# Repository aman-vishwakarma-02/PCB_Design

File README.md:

# PCB Design Projects  
**From Concept to Copper Board — A Small Beginning**

## About
This repository contains PCB design projects developed using **KiCad** as part of my learning and professional journey. The focus is on schematic design, PCB layout, signal integrity considerations, and manufacturable board designs.

## Projects Included

### Arduino UNO Board
### ESP32

### L298N Motor Driver Module

### Four-Layer IoT Development Board
- Multi-layer PCB design  
- Focus on signal integrity and power distribution  
- Designed for IoT and embedded applications  

## Tools & Technologies
- KiCad (Schematic & PCB Layout)  
- Multi-layer PCB design  
- Signal Integrity (SI) basics  
- Power Distribution Network (PDN)  
- DFM / DFA considerations  

## Learning Outcomes
- Understanding the PCB design workflow  
- Component placement and routing techniques  
- Designing manufacturable and reliable boards  
- Exposure to embedded and IoT hardware design

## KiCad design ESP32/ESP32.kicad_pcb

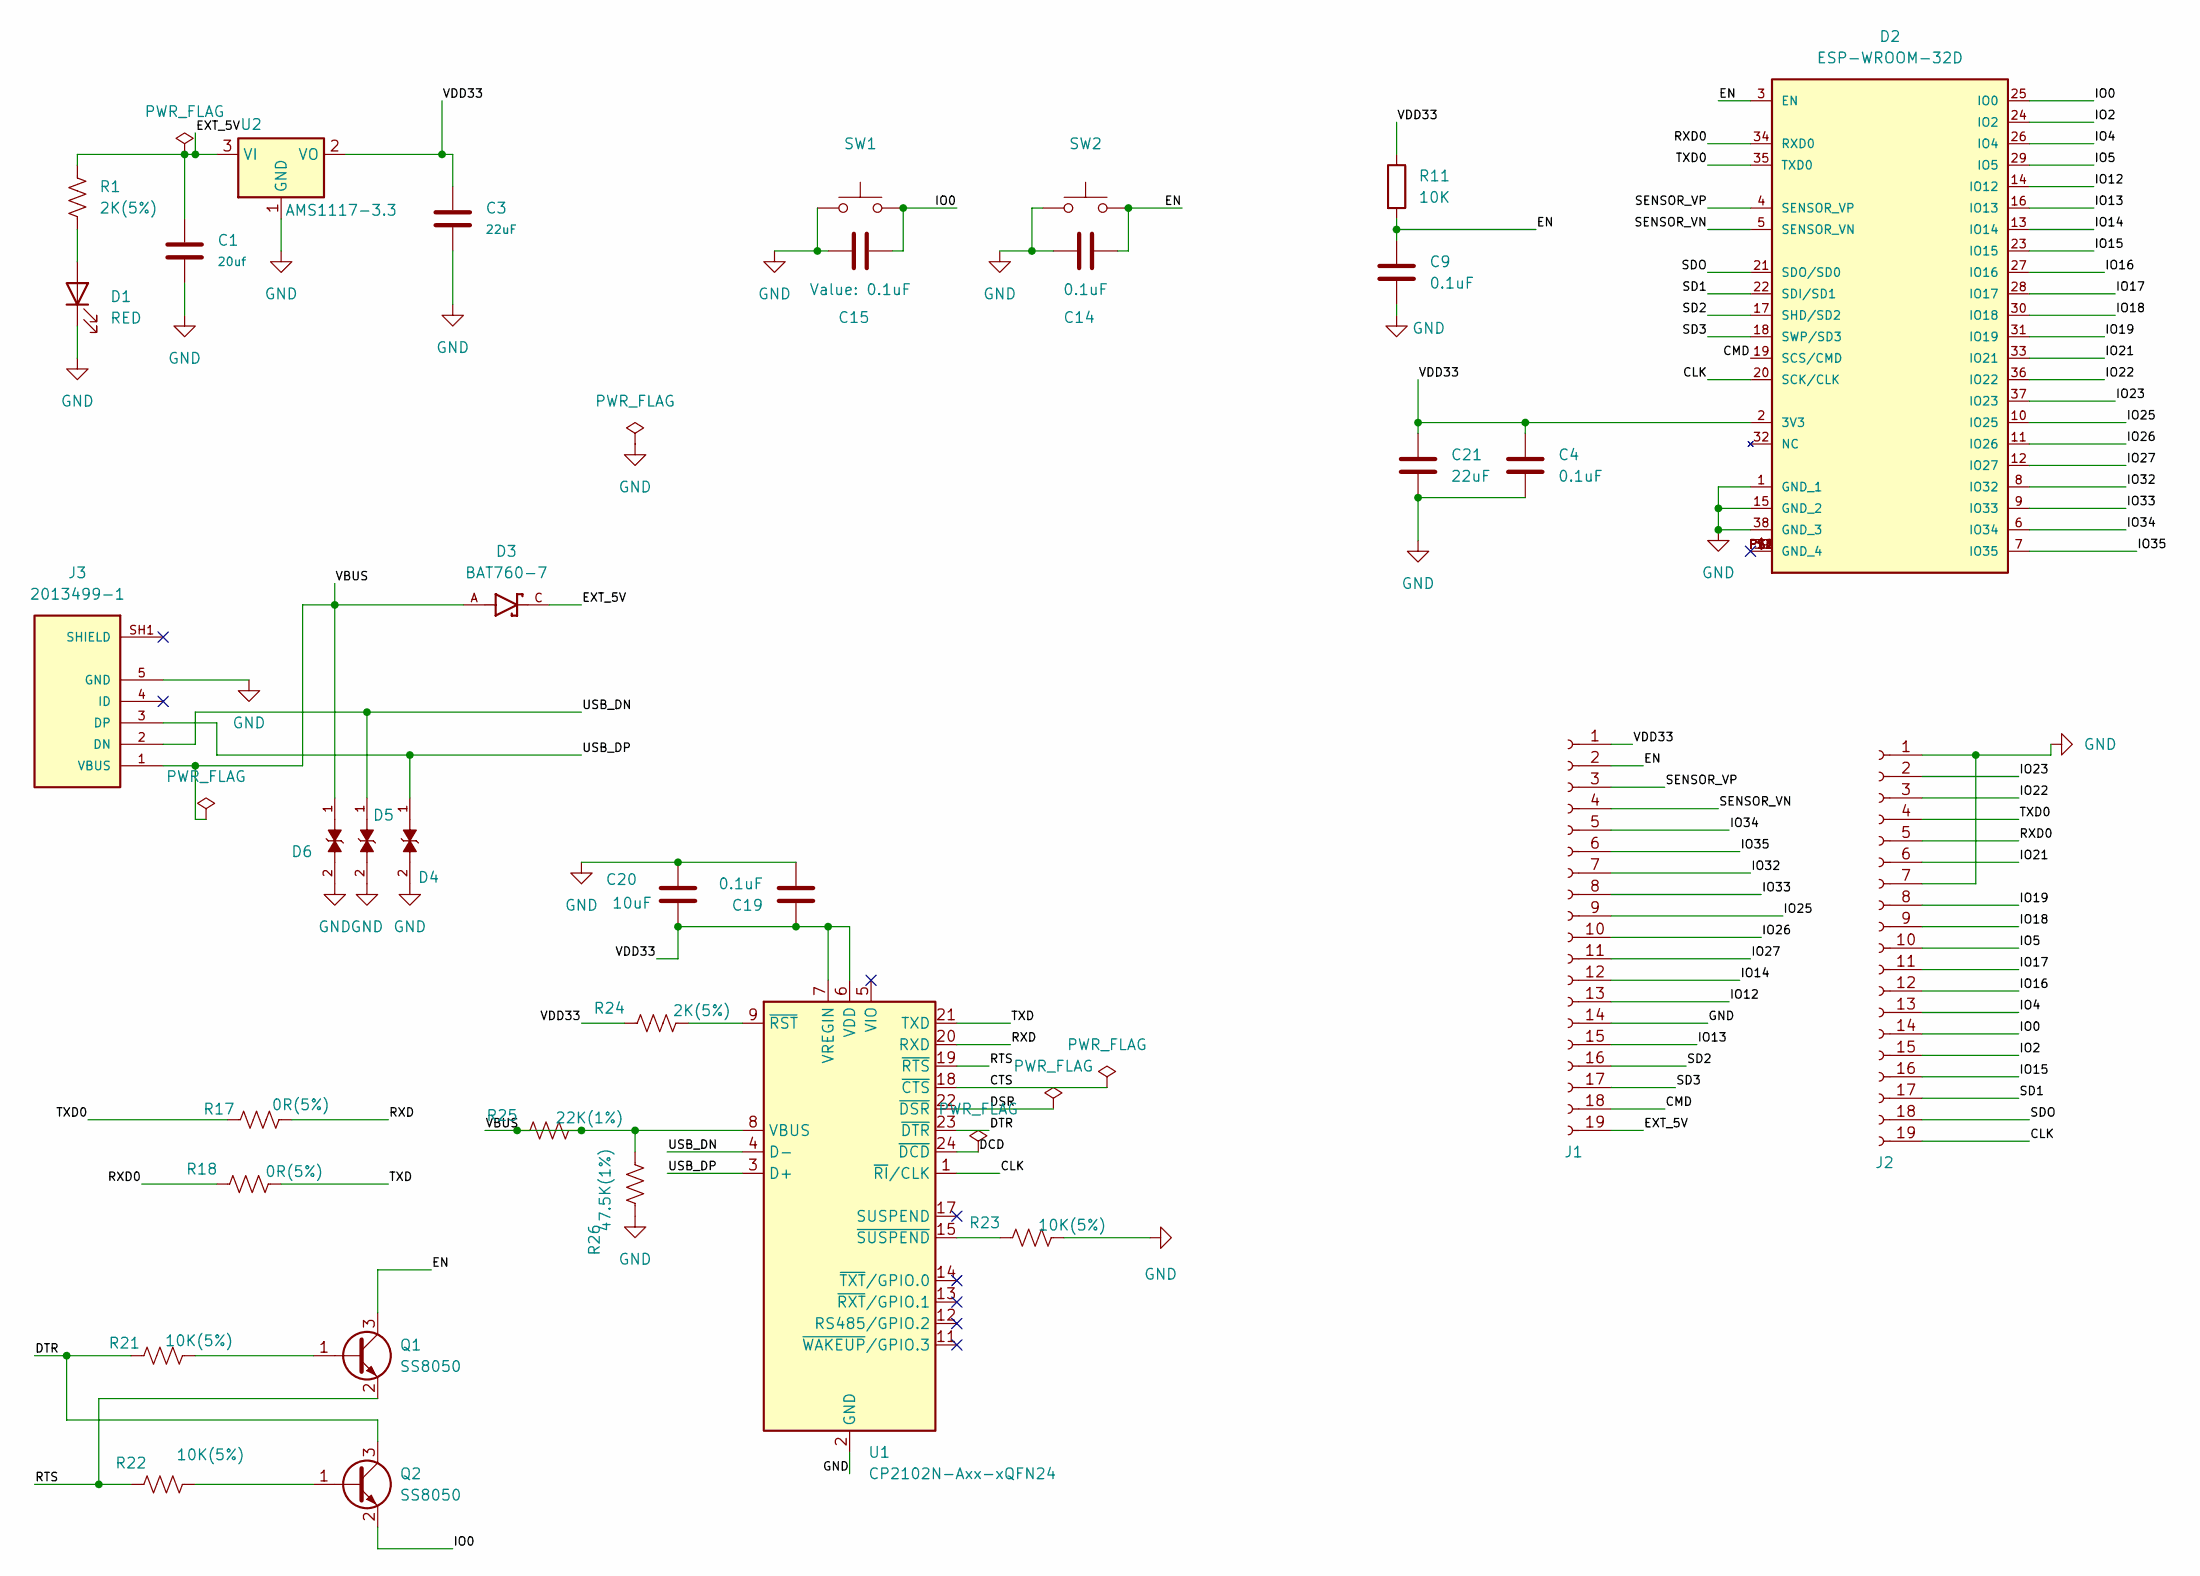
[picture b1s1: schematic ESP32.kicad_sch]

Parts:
C1: 20uf; C_0201_0603Metric
C3, C21: 22uF; C_0201_0603Metric
C4, C9, C14, C15, C19: 0.1uF; C_01005_0402Metric
C20: 10uF; C_0201_0603Metric
D1: RED; D_0201_0603Metric
D2: ESP-WROOM-32D; ESPWROOM32D; MOUSER_PART_NUMBER 356-ESP-WROOM-32D
D3: BAT760-7; SOD2513X120N; PARTREV 9-2
D4, D5, D6: LESD5D5.0CT1G; TVS_LESD5D5.0CT1G; PARTREV O
J1, J2: PinHeader_1x19_P2.54mm_Vertical
J3: 2013499-1; USB_Micro-B_Molex_47346-0001; PARTREV B5
Q1, Q2: SS8050; SOT-23
R1, R24: 2K(5%); R_01005_0402Metric
R11: 10K; R_01005_0402Metric
R17, R18: 0R(5%); R_01005_0402Metric
R21, R22, R23: 10K(5%); R_01005_0402Metric
R25: 22K(1%); R_01005_0402Metric
R26: 47.5K(1%); R_01005_0402Metric
SW1, SW2: SW_Push; SW_Push_SPST_NO_Alps_SKRK
U1: CP2102N-Axx-xQFN24; QFN-24-1EP_4x4mm_P0.5mm_EP2.6x2.6mm
U2: AMS1117-3.3; SOT-223-3_TabPin2

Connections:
/CLK: D2.20 (SCK/CLK), J2.19, U1.1 (~RI/CLK)
/CMD: D2.19 (SCS/CMD), J1.18
/CTS: U1.18 (~CTS)
/DCD: U1.24 (~DCD)
/DSR: U1.22 (~DSR)
/DTR: Q2.3 (C), R21.1, U1.23 (~DTR)
/EN: C9.1, C14.2, D2.3 (EN), J1.2, Q1.3 (C), R11.2, SW2.2
/EXT_5V: C1.1, D3.C, J1.19, R1.1, U2.3 (VI)
/IO0: C15.2, D2.25 (IO0), J2.14, Q2.2 (E), SW1.2
/IO2: D2.24 (IO2), J2.15
/IO4: D2.26 (IO4), J2.13
/IO5: D2.29 (IO5), J2.10
/IO12: D2.14 (IO12), J1.13
/IO13: D2.16 (IO13), J1.15
/IO14: D2.13 (IO14), J1.12
/IO15: D2.23 (IO15), J2.16
/IO16: D2.27 (IO16), J2.12
/IO17: D2.28 (IO17), J2.11
/IO18: D2.30 (IO18), J2.9
/IO19: D2.31 (IO19), J2.8
/IO21: D2.33 (IO21), J2.6
/IO22: D2.36 (IO22), J2.3
/IO23: D2.37 (IO23), J2.2
/IO25: D2.10 (IO25), J1.9
/IO26: D2.11 (IO26), J1.10
/IO27: D2.12 (IO27), J1.11
/IO32: D2.8 (IO32), J1.7
/IO33: D2.9 (IO33), J1.8
/IO34: D2.6 (IO34), J1.5
/IO35: D2.7 (IO35), J1.6
/RTS: Q1.2 (E), R22.1, U1.19 (~RTS)
/RXD: R17.2, U1.20 (RXD)
/RXD0: D2.34 (RXD0), J2.5, R18.1
/SD1: D2.22 (SDI/SD1), J2.17
/SD2: D2.17 (SHD/SD2), J1.16
/SD3: D2.18 (SWP/SD3), J1.17
/SDO: D2.21 (SDO/SD0), J2.18
/SENSOR_VN: D2.5 (SENSOR_VN), J1.4
/SENSOR_VP: D2.4 (SENSOR_VP), J1.3
/TXD: R18.2, U1.21 (TXD)
/TXD0: D2.35 (TXD0), J2.4, R17.1
/USB_DN: D5.1, J3.2 (DN), U1.4 (D-)
/USB_DP: D4.1, J3.3 (DP), U1.3 (D+)
/VBUS: D3.A, D6.1, J3.1 (VBUS), R25.1, R25.2, R26.2, U1.8 (VBUS)
/VDD33: C3.1, C4.1, C19.1, C20.1, C21.1, D2.2 (3V3), J1.1, R11.1, R24.1, U1.6 (VDD), U1.7 (VREGIN), U2.2 (VO); also elsewhere on the board
GND: C1.2, C3.2, C4.2, C9.2, C14.1, C15.1, C19.2, C20.2, C21.2, D1.1 (K), D2.1 (GND_1), D2.15 (GND_2), D2.38 (GND_3), D4.2, D5.2, D6.2, J1.14, J2.1, J2.7, J3.5 (GND), R23.2, R26.1, SW1.1, SW2.1, U1.2 (GND), U1.25 (GND), U2.1 (GND); also elsewhere on the board
unnamed: D1.2 (A), R1.2
unnamed: Q1.1 (B), R21.2
unnamed: Q2.1 (B), R22.2
unnamed: R24.2, U1.9 (~RST)
unnamed: R23.1, U1.15 (~SUSPEND)

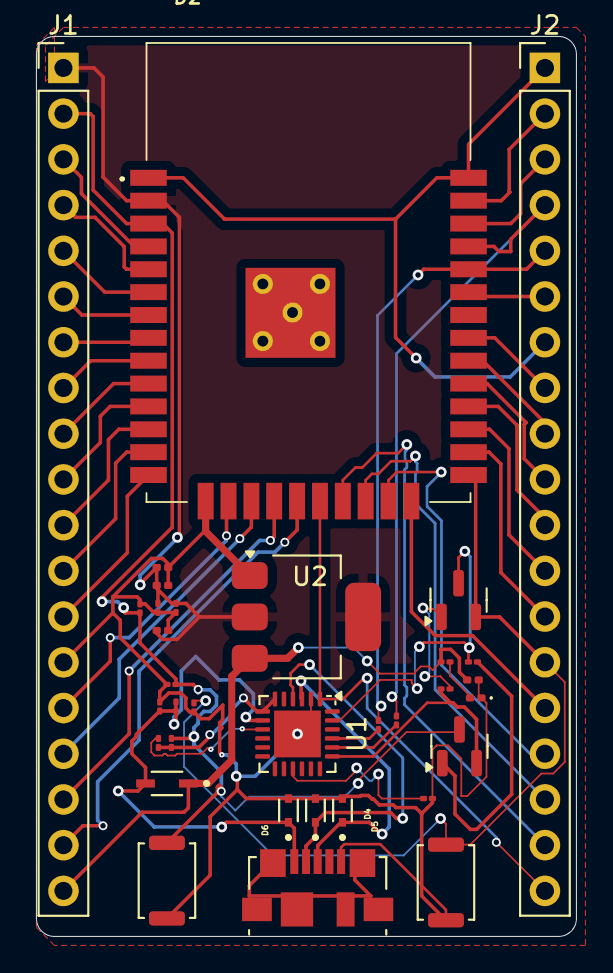
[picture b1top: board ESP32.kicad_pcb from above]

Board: 2 copper layers, 30.0 x 50.0 mm, 34 parts (0 on the bottom side), 48 nets.

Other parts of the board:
C: 22uF; C_0201_0603Metric

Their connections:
/VDD33: C.1; also elsewhere on the board
GND: C.2; also elsewhere on the board

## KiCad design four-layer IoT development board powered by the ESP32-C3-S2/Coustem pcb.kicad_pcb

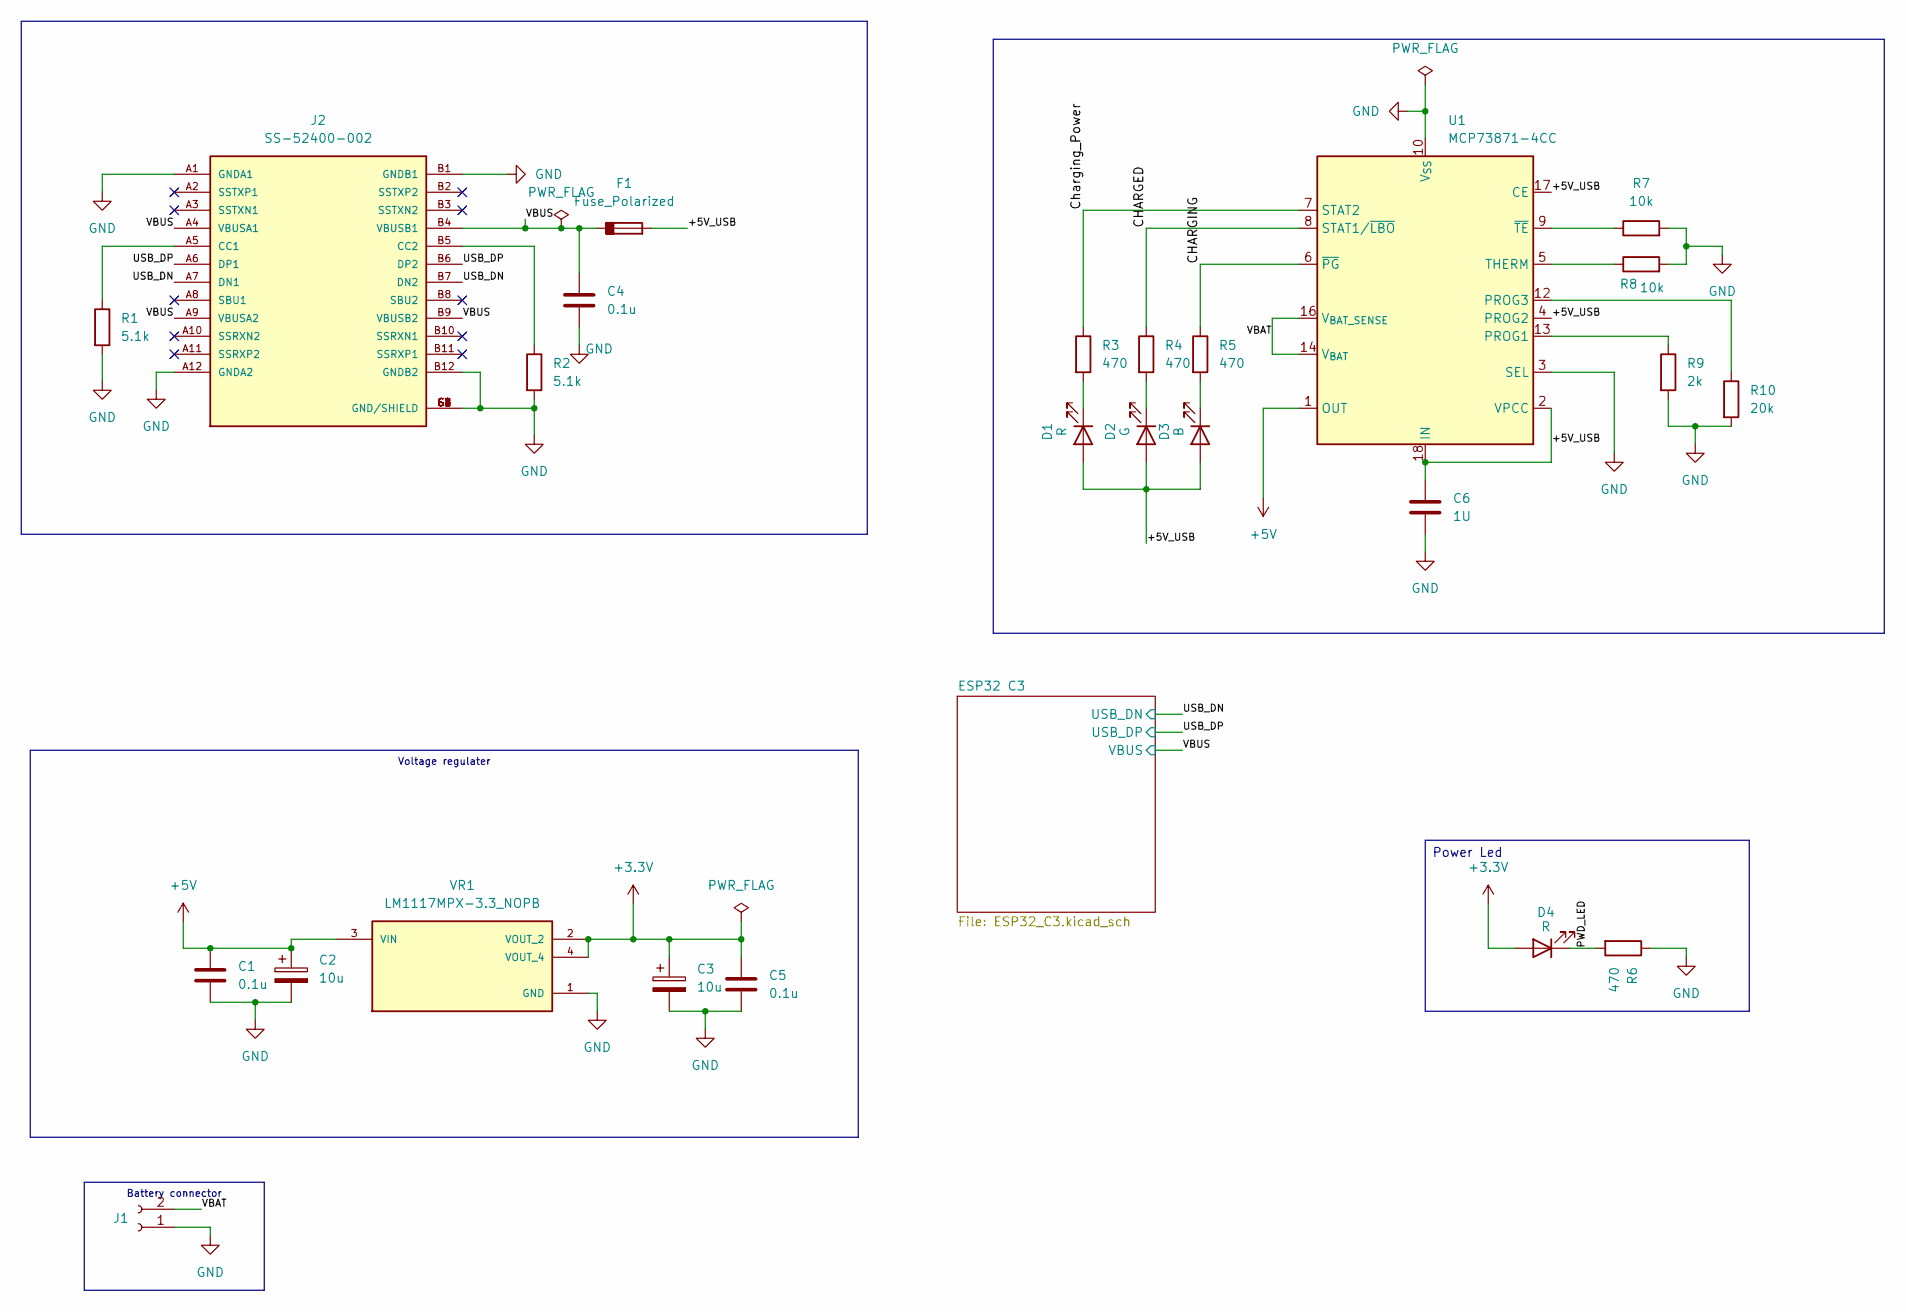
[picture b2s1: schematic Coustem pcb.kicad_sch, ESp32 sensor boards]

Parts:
C1, C4, C5: 0.1u; C_0805_2012Metric
C2, C3: 10u; CP_EIA-2012-15_AVX-P_HandSolder
C6: 1U; C_0805_2012Metric
D1, D4: R; LED_0805_2012Metric
D2: G; LED_0805_2012Metric
D3: B; LED_0805_2012Metric
F1: Fuse_Polarized; Fuse_1206_3216Metric
J1: Conn_01x02_Socket; JST_EH_B2B-EH-A_1x02_P2.50mm_Vertical
J2: SS-52400-002; BELFUSE_SS-52400-002; PARTREV A0
R1, R2: 5.1k; R_0805_2012Metric_Pad1.20x1.40mm_HandSolder
R3, R4, R5, R6: 470; R_0805_2012Metric_Pad1.20x1.40mm_HandSolder
R7, R8: 10k; R_0805_2012Metric_Pad1.20x1.40mm_HandSolder
R9: 2k; R_0805_2012Metric_Pad1.20x1.40mm_HandSolder
R10: 20k; R_0805_2012Metric_Pad1.20x1.40mm_HandSolder
U1: MCP73871-4CC; QFN-20-1EP_4x4mm_P0.5mm_EP2.5x2.5mm
VR1: LM1117MPX-3.3_NOPB; VREG_LM1117MPX-3.3_NOPB; PARTREV O

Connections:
+3.3V: C3.1, C5.1, D4.2 (A), VR1.2 (VOUT_2), VR1.4 (VOUT_4); also elsewhere on the board
+5V: C1.1, C2.1, U1.1 (OUT), U1.20 (OUT), VR1.3 (VIN)
/+5V_USB: C6.1, D1.2 (A), D2.2 (A), D3.2 (A), F1.2, U1.2 (VPCC), U1.4 (PROG2), U1.17 (CE), U1.18 (IN), U1.19 (IN)
/CHARGED: R4.1, U1.8 (STAT1/~LBO)
/CHARGING: R5.1, U1.6 (~PG)
/Charging_Power: R3.1, U1.7 (STAT2)
/PWD_LED: D4.1 (K), R6.2
/USB_DN: J2.A7 (DN1), J2.B7 (DN2); also elsewhere on the board
/USB_DP: J2.A6 (DP1), J2.B6 (DP2); also elsewhere on the board
/VBAT: J1.2, U1.14 (V_{BAT}), U1.15 (V_{BAT}), U1.16 (V_{BAT_SENSE})
/VBUS: C4.1, F1.1, J2.A4 (VBUSA1), J2.A9 (VBUSA2), J2.B4 (VBUSB1), J2.B9 (VBUSB2); also elsewhere on the board
GND: C1.2, C2.2, C3.2, C4.2, C5.2, C6.2, J1.1, J2.A1 (GNDA1), J2.A12 (GNDA2), J2.B1 (GNDB1), J2.B12 (GNDB2), J2.G1 (GND/SHIELD), J2.G2 (GND/SHIELD), J2.G3 (GND/SHIELD), J2.G4 (GND/SHIELD), J2.S1 (GND/SHIELD), J2.S2 (GND/SHIELD), J2.S3 (GND/SHIELD), J2.S4 (GND/SHIELD), R1.2, R2.2, R6.1, R7.2, R8.2, R9.2, R10.2, U1.3 (SEL), U1.10 (V_{SS}), U1.11 (V_{SS}), U1.21 (V_{SS}), VR1.1 (GND); also elsewhere on the board
unnamed: D1.1 (K), R3.2
unnamed: D2.1 (K), R4.2
unnamed: D3.1 (K), R5.2
unnamed: J2.A5 (CC1), R1.1
unnamed: J2.B5 (CC2), R2.1
unnamed: R9.1, U1.13 (PROG1)
unnamed: R10.1, U1.12 (PROG3)
unnamed: R8.1, U1.5 (THERM)
unnamed: R7.1, U1.9 (~TE)

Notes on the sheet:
Power Led
Voltage regulater
Battery connector

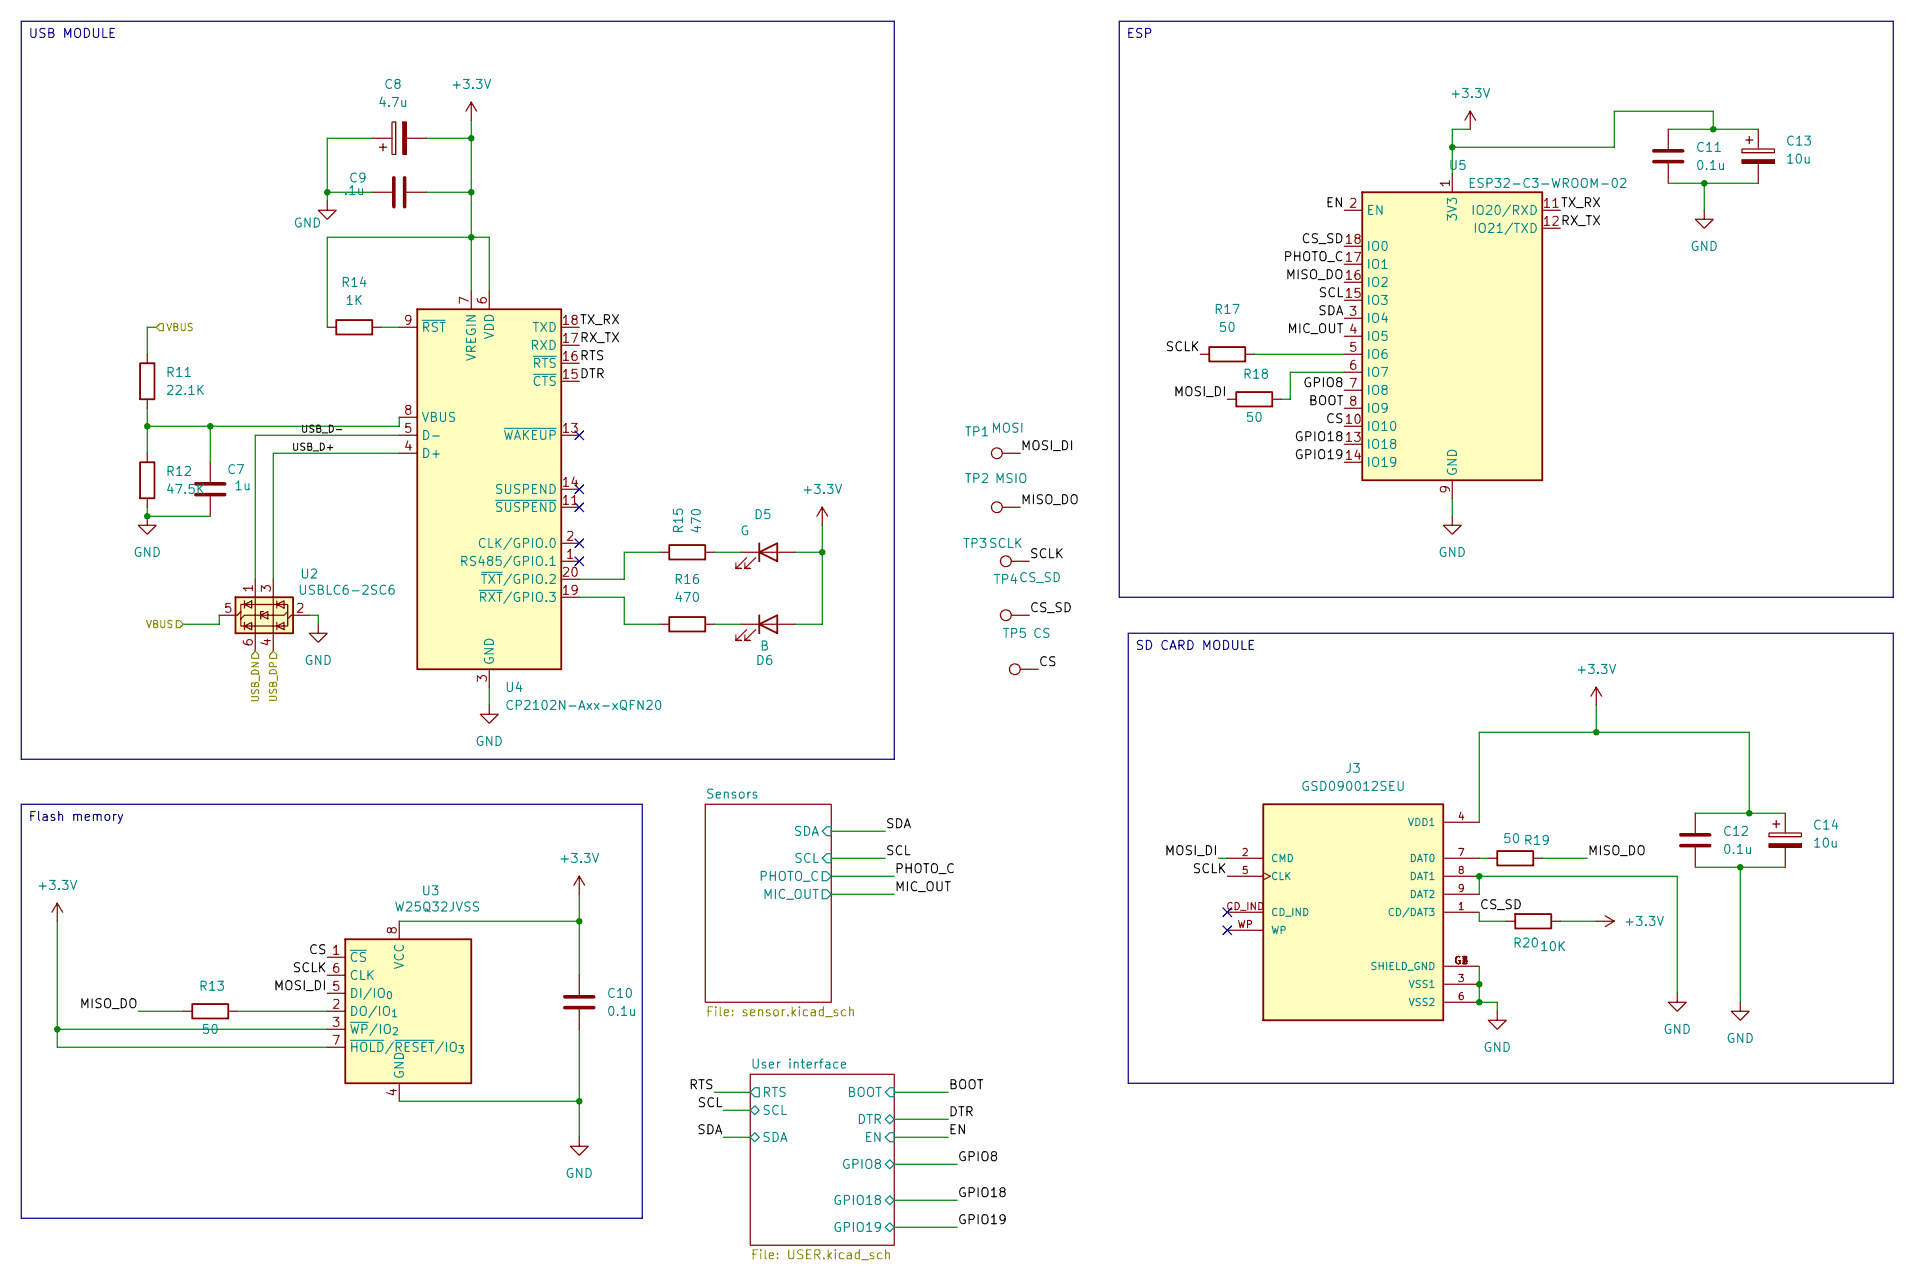
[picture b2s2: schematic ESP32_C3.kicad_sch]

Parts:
C7: 1u; C_0805_2012Metric
C8: 4.7u; CP_EIA-2012-12_Kemet-R_HandSolder
C9: .1u; C_0805_2012Metric
C10, C11, C12: 0.1u; C_0805_2012Metric
C13: 10u; CP_EIA-2012-12_Kemet-R_HandSolder
C14: 10u; C_0805_2012Metric
D5: G; LED_0805_2012Metric
D6: B; LED_0805_2012Metric
J3: GSD090012SEU; AMPHENOL_GSD090012SEU; PARTREV E
R11: 22.1K; R_0805_2012Metric_Pad1.20x1.40mm_HandSolder
R12: 47.5K; R_0805_2012Metric_Pad1.20x1.40mm_HandSolder
R13, R17, R18, R19: 50; R_0805_2012Metric_Pad1.20x1.40mm_HandSolder
R14: 1K; R_0805_2012Metric_Pad1.20x1.40mm_HandSolder
R15, R16: 470; R_0805_2012Metric_Pad1.20x1.40mm_HandSolder
R20: 10K; R_0805_2012Metric_Pad1.20x1.40mm_HandSolder
TP1: MOSI; TestPoint_Pad_D1.0mm
TP2: MSIO; TestPoint_Pad_D1.0mm
TP3: SCLK; TestPoint_Pad_D1.0mm
TP4: CS_SD; TestPoint_Pad_D1.0mm
TP5: CS; TestPoint_Pad_D1.0mm
U2: USBLC6-2SC6; SOT-23-6
U3: W25Q32JVSS; SOIC-8_5.3x5.3mm_P1.27mm
U4: CP2102N-Axx-xQFN20; SiliconLabs_QFN-20-1EP_3x3mm_P0.5mm_EP1.8x1.8mm
U5: ESP32-C3-WROOM-02

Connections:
+3.3V: C8.2, C9.2, C10.1, C11.1, C12.1, C13.1, C14.1, D5.2 (A), D6.2 (A), J3.4 (VDD1), R14.1, R20.1, U3.3 (~WP/IO_{2}), U3.7 (~HOLD/~RESET/IO_{3}), U3.8 (VCC), U4.6 (VDD), U4.7 (VREGIN), U5.1 (3V3); also elsewhere on the board
/ESP32 C3/BOOT: U5.8 (IO9); also elsewhere on the board
/ESP32 C3/CS: TP5.1, U3.1 (~CS), U5.10 (IO10)
/ESP32 C3/CS_SD: J3.1 (CD/DAT3), R20.2, TP4.1, U5.18 (IO0)
/ESP32 C3/DTR: U4.15 (~CTS); also elsewhere on the board
/ESP32 C3/EN: U5.2 (EN); also elsewhere on the board
/ESP32 C3/GPIO8: U5.7 (IO8); also elsewhere on the board
/ESP32 C3/GPIO18: U5.13 (IO18); also elsewhere on the board
/ESP32 C3/GPIO19: U5.14 (IO19); also elsewhere on the board
/ESP32 C3/MIC_OUT: U5.4 (IO5); also elsewhere on the board
/ESP32 C3/MISO_DO: R13.1, R19.2, TP2.1, U5.16 (IO2)
/ESP32 C3/MOSI_DI: J3.2 (CMD), R18.1, TP1.1, U3.5 (DI/IO_{0})
/ESP32 C3/PHOTO_C: U5.17 (IO1); also elsewhere on the board
/ESP32 C3/RTS: U4.16 (~RTS); also elsewhere on the board
/ESP32 C3/RX_TX: U4.17 (RXD), U5.12 (IO21/TXD)
/ESP32 C3/SCL: U5.15 (IO3); also elsewhere on the board
/ESP32 C3/SCLK: J3.5 (CLK), R17.1, TP3.1, U3.6 (CLK)
/ESP32 C3/SDA: U5.3 (IO4); also elsewhere on the board
/ESP32 C3/TX_RX: U4.18 (TXD), U5.11 (IO20/RXD)
/ESP32 C3/USB_D+: U2.3 (I/O2), U4.4 (D+)
/ESP32 C3/USB_D-: U2.1 (I/O1), U4.5 (D-)
/USB_DN: U2.6 (I/O1); also elsewhere on the board
/USB_DP: U2.4 (I/O2); also elsewhere on the board
/VBUS: R11.1, U2.5 (VBUS); also elsewhere on the board
GND: C7.2, C8.1, C9.1, C10.2, C11.2, C12.2, C13.2, C14.2, J3.3 (VSS1), J3.6 (VSS2), J3.8 (DAT1), J3.9 (DAT2), J3.G1 (SHIELD_GND), J3.G2 (SHIELD_GND), J3.G3 (SHIELD_GND), J3.G4 (SHIELD_GND), R12.2, U2.2 (GND), U3.4 (GND), U4.3 (GND), U4.12 (GND), U4.21 (GND), U5.9 (GND), U5.19 (GND); also elsewhere on the board
unnamed: D5.1 (K), R15.2
unnamed: D6.1 (K), R16.2
unnamed: J3.7 (DAT0), R19.1
unnamed: R13.2, U3.2 (DO/IO_{1})
unnamed: C7.1, R11.2, R12.1, U4.8 (VBUS)
unnamed: R14.2, U4.9 (~RST)
unnamed: R16.1, U4.19 (~RXT/GPIO.3)
unnamed: R15.1, U4.20 (~TXT/GPIO.2)
unnamed: R17.2, U5.5 (IO6)
unnamed: R18.2, U5.6 (IO7)

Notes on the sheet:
SD CARD MODULE
ESP
Flash memory
USB MODULE

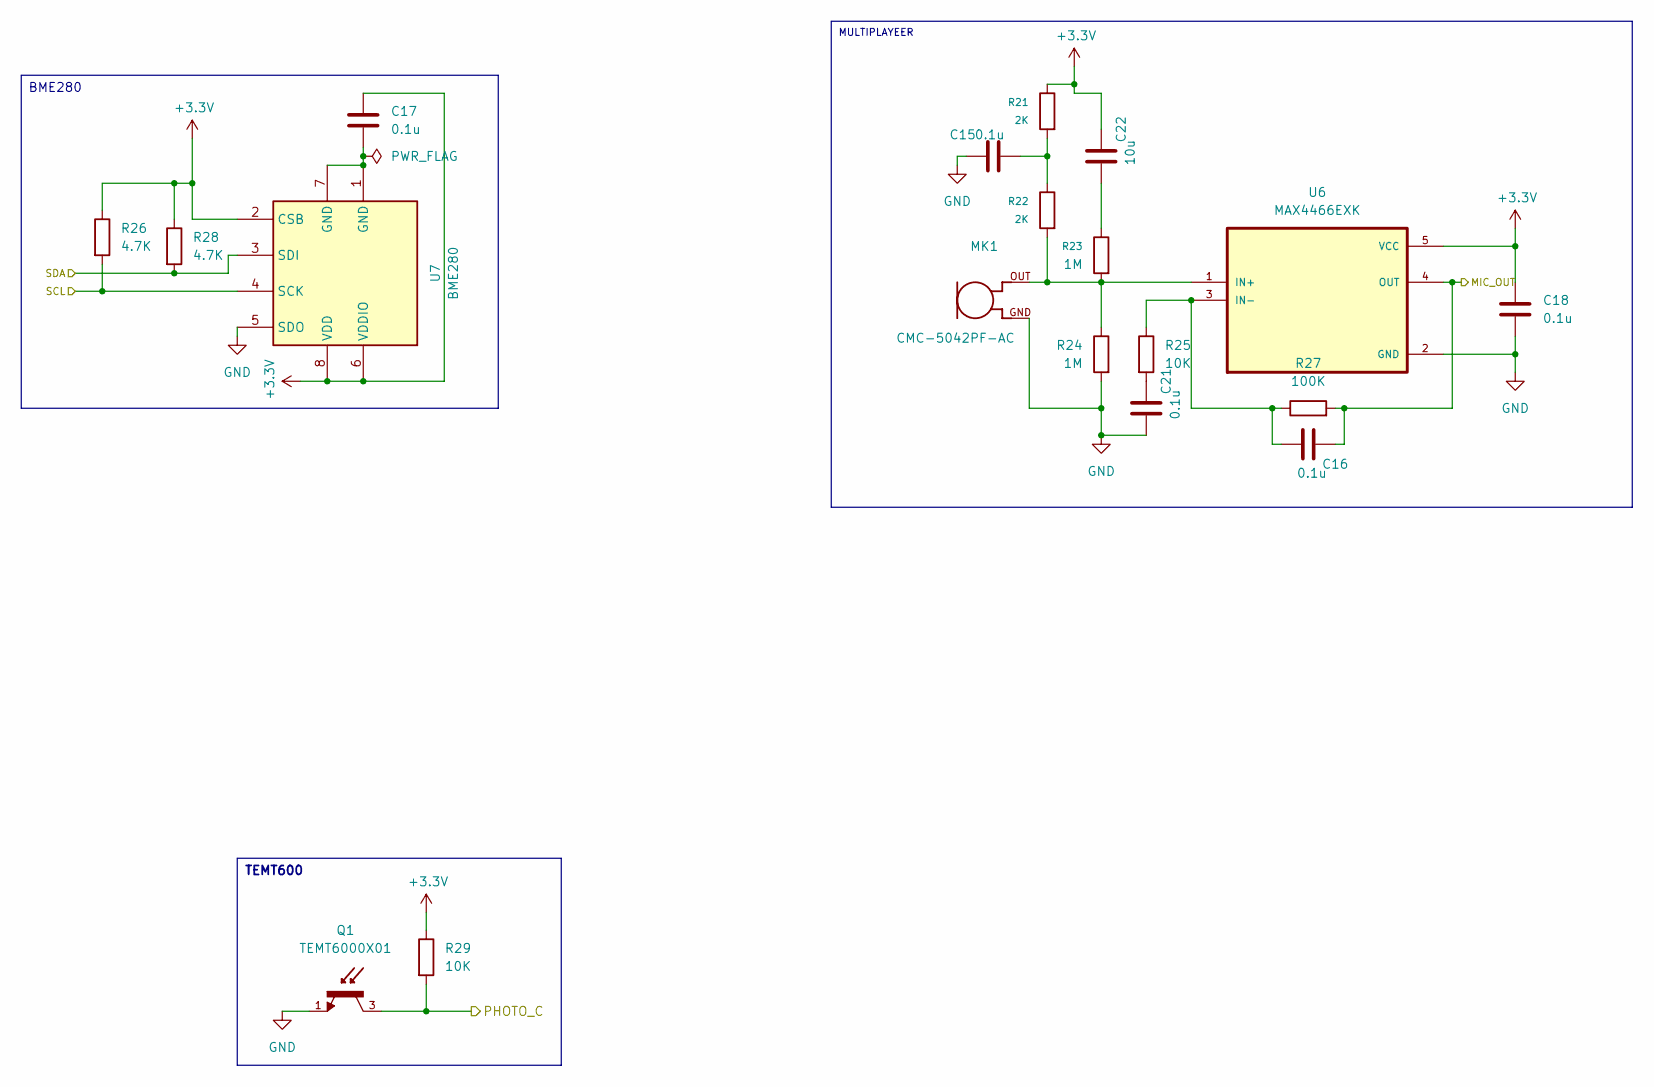
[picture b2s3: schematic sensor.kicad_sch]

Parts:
C15, C16, C17, C18, C21: 0.1u; C_0805_2012Metric
C22: 10u; C_0805_2012Metric
MK1: CMC-5042PF-AC; CUI_CMC-5042PF-AC
Q1: TEMT6000X01; TRANS_TEMT6000X01; PARTREV 1.9; DigiKey_Part_Number 751-1055-1-ND
R21, R22: 2K; R_0805_2012Metric_Pad1.20x1.40mm_HandSolder
R23, R24: 1M; R_0805_2012Metric_Pad1.20x1.40mm_HandSolder
R25, R29: 10K; R_0805_2012Metric_Pad1.20x1.40mm_HandSolder
R26, R28: 4.7K; R_0805_2012Metric_Pad1.20x1.40mm_HandSolder
R27: 100K; R_0805_2012Metric_Pad1.20x1.40mm_HandSolder
U6: MAX4466EXK; SOT65P210X110-5N
U7: BME280; Bosch_LGA-8_2.5x2.5mm_P0.65mm_ClockwisePinNumbering

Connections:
+3.3V: C17.2, C18.2, C22.1, R21.1, R26.1, R28.1, R29.1, U6.5 (VCC), U7.2 (CSB), U7.6 (VDDIO), U7.8 (VDD); also elsewhere on the board
/ESP32 C3/MIC_OUT: C16.1, R27.2, U6.4 (OUT); also elsewhere on the board
/ESP32 C3/PHOTO_C: Q1.3, R29.2; also elsewhere on the board
/ESP32 C3/SCL: R26.2, U7.4 (SCK); also elsewhere on the board
/ESP32 C3/SDA: R28.2, U7.3 (SDI); also elsewhere on the board
GND: C15.2, C18.1, C21.2, MK1.GND, Q1.1, R24.2, U6.2 (GND), U7.5 (SDO); also elsewhere on the board
unnamed: C15.1, R21.2, R22.1
unnamed: C17.1, U7.1 (GND), U7.7 (GND)
unnamed: C21.1, R25.2
unnamed: C22.2, R23.1
unnamed: MK1.OUT, R22.2, R23.2, R24.1, U6.1 (IN+)
unnamed: C16.2, R25.1, R27.1, U6.3 (IN-)

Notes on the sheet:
MULTIPLAYEER
TEMT600
BME280

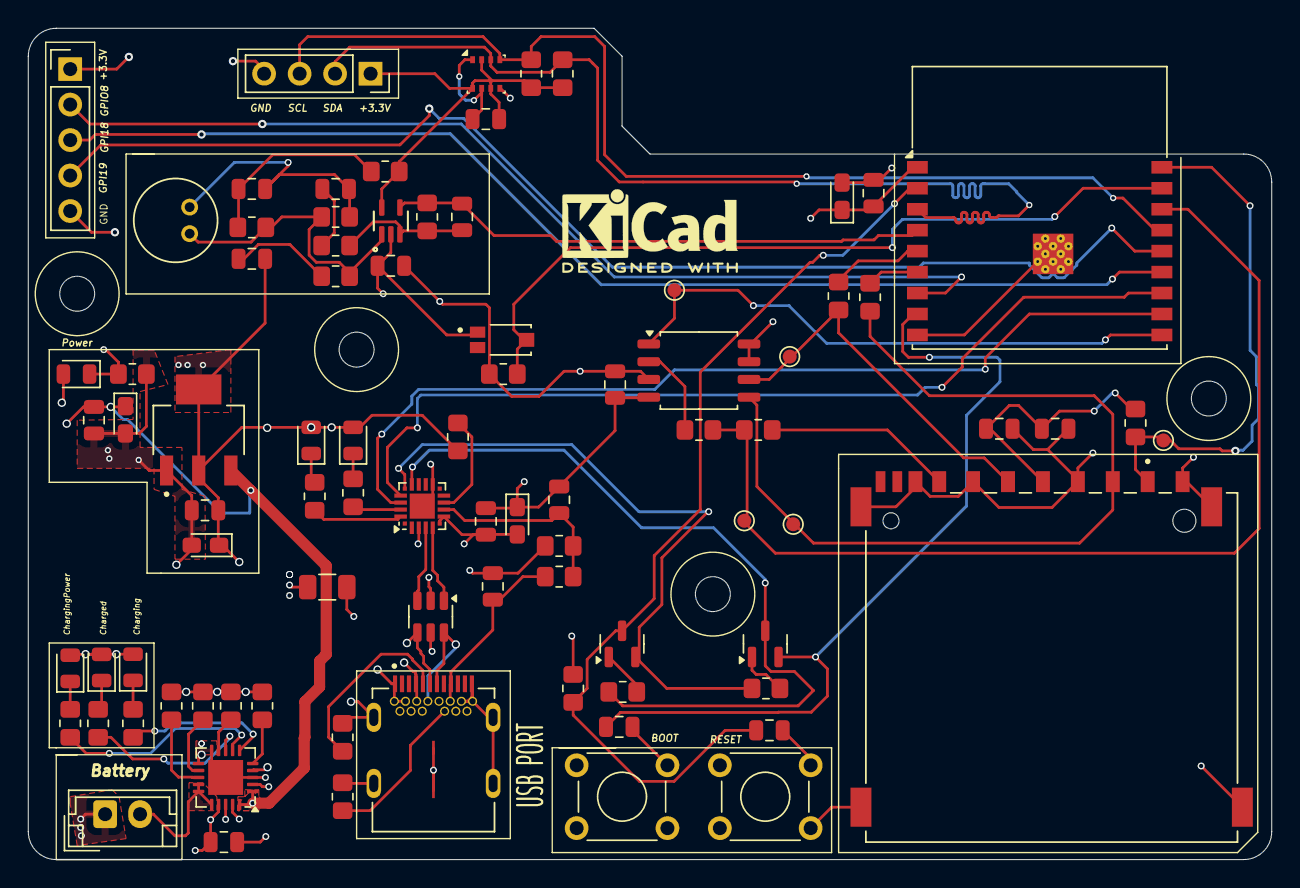
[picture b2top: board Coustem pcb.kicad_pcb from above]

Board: 4 copper layers, 89.0 x 59.5 mm, 85 parts (0 on the bottom side), 59 nets.

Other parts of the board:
C19: 0.1uf; C_0805_2012Metric
C20: 1uf; C_0805_2012Metric
J4: Conn_01x05_Pin; PinHeader_1x05_P2.54mm_Vertical
J5: Conn_01x04_Pin; PinSocket_1x04_P2.54mm_Vertical
Q2, Q3: BC817; SOT-23
R30, R31, R32: 10K; R_0805_2012Metric_Pad1.20x1.40mm_HandSolder
SW1: BOOT; SW_TH_Tactile_Omron_B3F-107x
SW2: RESET; SW_TH_Tactile_Omron_B3F-107x

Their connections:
+3.3V: J4.1, J5.1, R32.2; also elsewhere on the board
/ESP32 C3/BOOT: C19.1, Q3.2 (E); also elsewhere on the board
/ESP32 C3/DTR: Q3.3 (C), R30.1; also elsewhere on the board
/ESP32 C3/EN: C20.1, Q2.3 (C), R32.1; also elsewhere on the board
/ESP32 C3/GPIO8: J4.2; also elsewhere on the board
/ESP32 C3/GPIO18: J4.3; also elsewhere on the board
/ESP32 C3/GPIO19: J4.4; also elsewhere on the board
/ESP32 C3/RTS: Q2.2 (E), R31.1; also elsewhere on the board
/ESP32 C3/SCL: J5.3; also elsewhere on the board
/ESP32 C3/SDA: J5.2; also elsewhere on the board
GND: C19.2, C20.2, J4.5, J5.4, SW1.1, SW1.2, SW2.1, SW2.2; also elsewhere on the board
unnamed: Q2.1 (B), R30.2
unnamed: Q3.1 (B), R31.2

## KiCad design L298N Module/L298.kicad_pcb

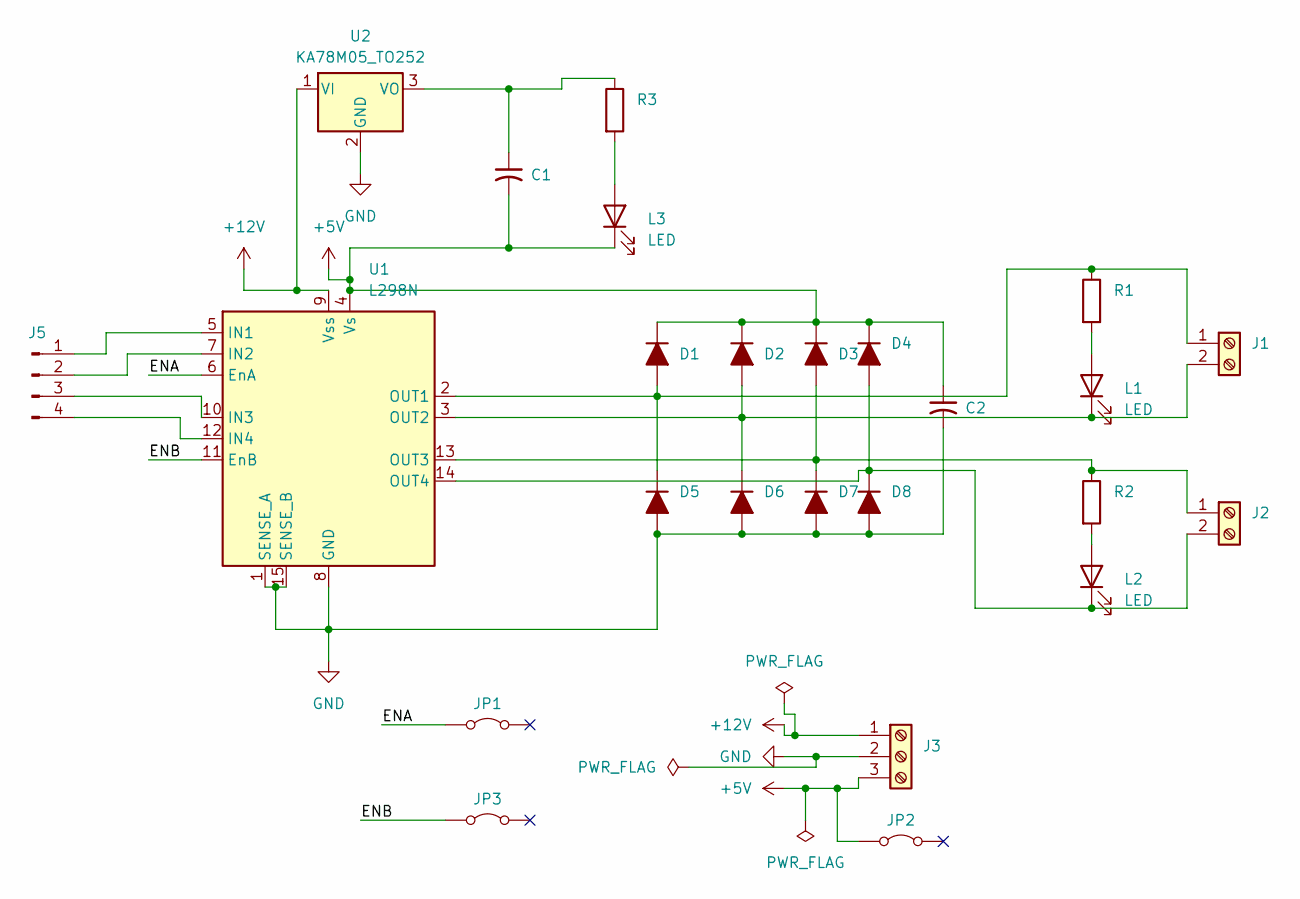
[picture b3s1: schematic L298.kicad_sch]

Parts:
C1, C2: 200uf; C_Elec_3x5.4
D1, D2, D3, D4, D5, D6, D7, D8: D_Filled; D_2010_5025Metric
J1, J2: Screw_Terminal_01x02; TerminalBlock_Phoenix_MPT-0,5-2-2.54_1x02_P2.54mm_Horizontal
J3: Screw_Terminal_01x03; TerminalBlock_Phoenix_MPT-0,5-3-2.54_1x03_P2.54mm_Horizontal
J5: Conn_02x04_Odd_Even; PinHeader_1x04_P2.54mm_Vertical
JP1, JP2, JP3: Jumper_2_Bridged; TestPoint_2Pads_Pitch2.54mm_Drill0.8mm
L1, L2, L3: LED; LED_0805_2012Metric
R1, R2, R3: R; R_0805_2012Metric
U1: L298N; TO-220-15_P2.54x5.08mm_StaggerOdd_Lead4.58mm_Vertical
U2: KA78M05_TO252; TO-252-2

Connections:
+5V: C1.2, C2.1, D1.1 (K), D2.1 (K), D3.1 (K), D4.1 (K), J3.3, JP2.1 (A), L3.1 (K), U1.4 (Vs)
+12V: J3.1, U1.9 (Vss), U2.1 (VI)
/ENA: JP1.1 (A), U1.6 (EnA)
/ENB: JP3.1 (A), U1.11 (EnB)
GND: C2.2, D5.2 (A), D6.2 (A), D7.2 (A), D8.2 (A), J3.2, U1.1 (SENSE_A), U1.8 (GND), U1.15 (SENSE_B), U2.2 (GND)
unnamed: D1.2 (A), D5.1 (K), J1.1, R1.1, U1.2 (OUT1)
unnamed: D2.2 (A), D6.1 (K), J1.2, L1.1 (K), U1.3 (OUT2)
unnamed: D3.2 (A), D7.1 (K), J2.1, R2.1, U1.13 (OUT3)
unnamed: D4.2 (A), D8.1 (K), J2.2, L2.1 (K), U1.14 (OUT4)
unnamed: J5.1, U1.5 (IN1)
unnamed: J5.2, U1.7 (IN2)
unnamed: J5.3, U1.10 (IN3)
unnamed: J5.4, U1.12 (IN4)
unnamed: L1.2 (A), R1.2
unnamed: L2.2 (A), R2.2
unnamed: L3.2 (A), R3.2
unnamed: C1.1, R3.1, U2.3 (VO)

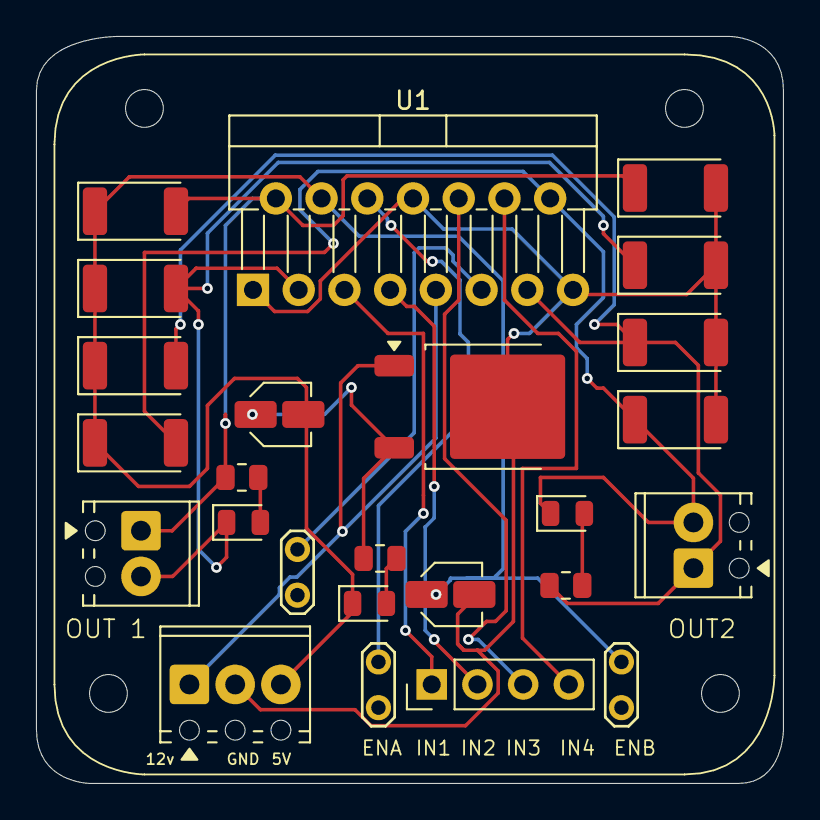
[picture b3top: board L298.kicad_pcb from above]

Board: 2 copper layers, 41.5 x 41.5 mm, 25 parts (0 on the bottom side), 17 nets.
